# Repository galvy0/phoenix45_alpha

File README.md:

# Phoenix45 Alpha Stagger PCB
Alpha stagger version of Phoenix45.  

## PCB
### Layout Options

## Middle Column Options
The middle column can be configured with either an OLED or a trackpoint module.  

### Middle Column Cover
Either case, I provide the files for a cover along with plate option to mount the cover.  
Using the cover would help fill/cover up the space between the plate and the top of the case and make the middle column look more flush with the top of the case (a.k.a it's just for aesthetics).  
To use the cover, you need M2 screws and standoffs - I find ~6 mm is a good length for the standoffs, though 7 mm also works well and gives enough space for the trackpoint module.  

### Trackpoint module
The only TP module compatible with this is the two-piece module found in ThinkPad T440/T450/T460/T470/T480, P52s, X240, X250, X260 X270 (according to https://deskthority.net/wiki/TrackPoint_Hardware).  
I just bought some replacement T440/T450 keyboards from Ebay and scavanged the TP modules.  
Steps (Very rough - I will try to take some photos for better instructions next time I build this):  
1. Unscrew the casing for the TP module.
2. Install a TP cover. This can be done later.    
Depending on the thickness of the cover, you may want to have hex nuts between the module and the cover so the TP sticks out as little as possible (mainly for aesthetics).  
3. Desolder all the lines and reconnect them using flexible wires so you can readjust the position of the TP module with the TP PCB.  
4. Refer to the pinouts from Deskthority to connect the pins on the TP PCB to the keyboard PCB.  
 
5. With the plate standoffs pre-installed, position the TP PCB slanted through the middle column.  

6. Install the TP cover to the plate.  
After all is done, it would look something like this: 

## QMK Firmware
https://github.com/galvy0/qmk_firmware/tree/galvy/keyboards/galvy/jd45_alpha

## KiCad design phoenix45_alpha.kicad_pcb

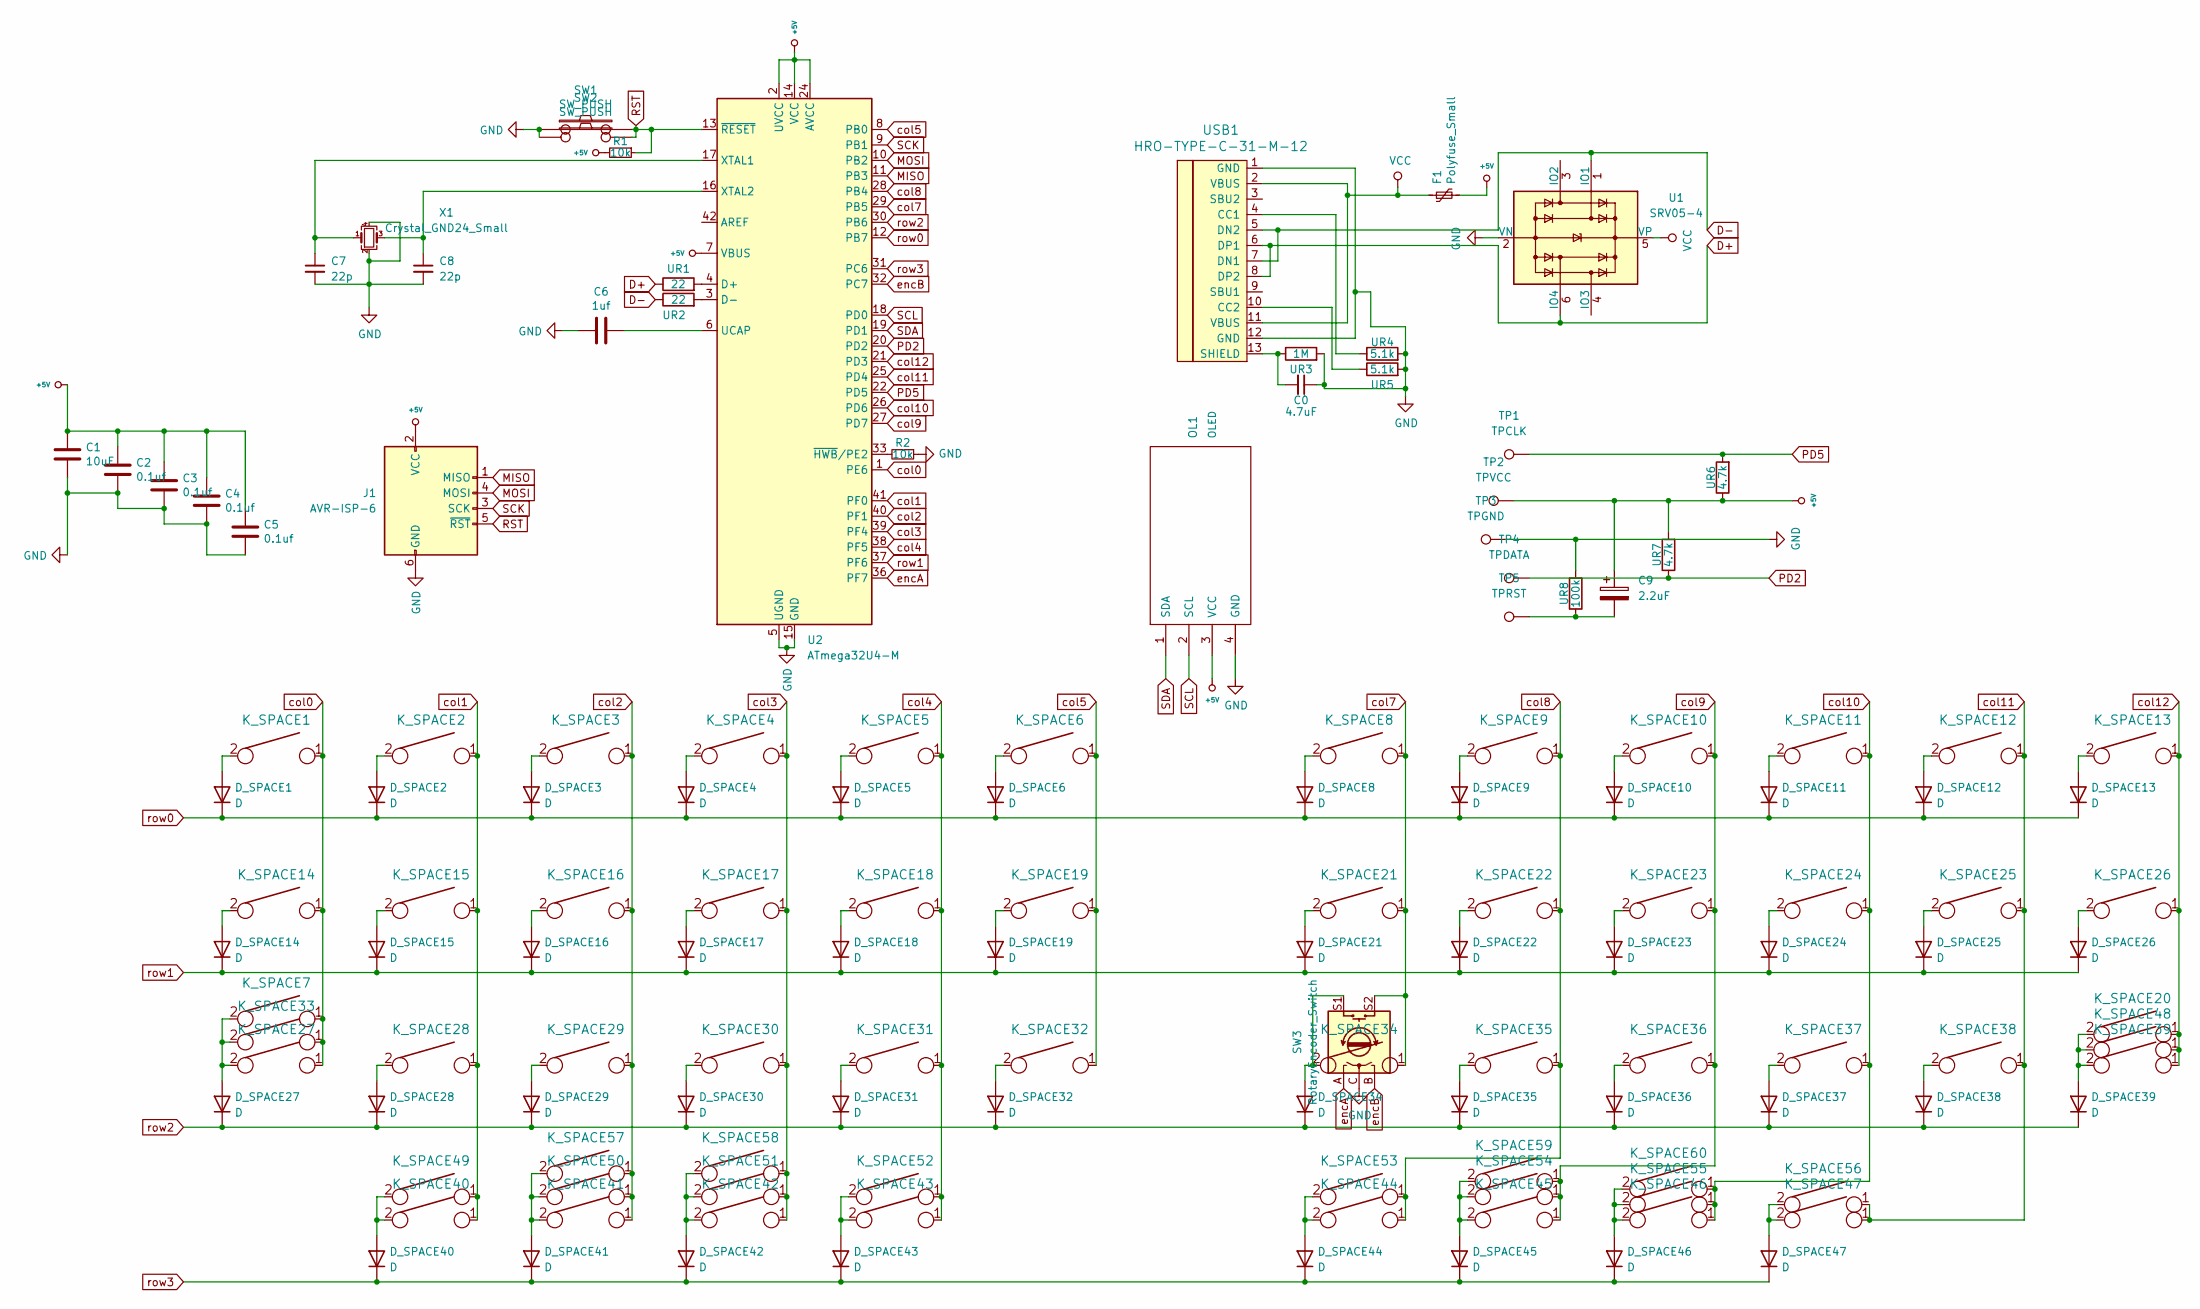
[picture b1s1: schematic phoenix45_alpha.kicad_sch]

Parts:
C0: 4.7uF; C_0805_2012Metric_Pad1.18x1.45mm_HandSolder
C1: 10uF; C_0805_2012Metric_Pad1.18x1.45mm_HandSolder
C2, C3, C4, C5: 0.1uf; C_0805_2012Metric_Pad1.18x1.45mm_HandSolder
C6: 1uf; C_0805_2012Metric_Pad1.18x1.45mm_HandSolder
C7, C8: 22p; C_0805_2012Metric_Pad1.18x1.45mm_HandSolder
C9: 2.2uF; C_0805_2012Metric_Pad1.18x1.45mm_HandSolder
D_SPACE1, D_SPACE2, D_SPACE3, D_SPACE4, D_SPACE5, D_SPACE6, D_SPACE8, D_SPACE9, D_SPACE10, D_SPACE11, D_SPACE12, D_SPACE13, D_SPACE14, D_SPACE15, D_SPACE16, D_SPACE17, D_SPACE18, D_SPACE19, D_SPACE21, D_SPACE22, D_SPACE23, D_SPACE24, D_SPACE25, D_SPACE26, D_SPACE27, D_SPACE28, D_SPACE29, D_SPACE30, D_SPACE31, D_SPACE32, D_SPACE34, D_SPACE35, D_SPACE36, D_SPACE37, D_SPACE38, D_SPACE39, D_SPACE40, D_SPACE41, D_SPACE42, D_SPACE43, D_SPACE44, D_SPACE45, D_SPACE46, D_SPACE47: D; D_SOD-123
F1: Polyfuse_Small; Fuse_1206_3216Metric_Pad1.42x1.75mm_HandSolder
J1: AVR-ISP-6; IDC-Header_2x03_P2.54mm_Vertical
K_SPACE1, K_SPACE2, K_SPACE3, K_SPACE4, K_SPACE5, K_SPACE6, K_SPACE8, K_SPACE9, K_SPACE10, K_SPACE11, K_SPACE12, K_SPACE13, K_SPACE14, K_SPACE15, K_SPACE16, K_SPACE17, K_SPACE18, K_SPACE19, K_SPACE21, K_SPACE22, K_SPACE23, K_SPACE24, K_SPACE25, K_SPACE26, K_SPACE27, K_SPACE28, K_SPACE29, K_SPACE30, K_SPACE31, K_SPACE32, K_SPACE34, K_SPACE35, K_SPACE36, K_SPACE37, K_SPACE38, K_SPACE39, K_SPACE41, K_SPACE46, K_SPACE50, K_SPACE51, K_SPACE54, K_SPACE55, K_SPACE58, K_SPACE59: KEYSW; MXOnly-1U-NoLED
K_SPACE7, K_SPACE20, K_SPACE52, K_SPACE53: KEYSW; MXOnly-1.5U-NoLED
K_SPACE33, K_SPACE40, K_SPACE42, K_SPACE45, K_SPACE47, K_SPACE48, K_SPACE57, K_SPACE60: KEYSW; MXOnly-1.25U-NoLED
K_SPACE43, K_SPACE44, K_SPACE49, K_SPACE56: KEYSW; MXOnly-1.75U-NoLED
OL1: OLED; OLED_v2
R1, R2: 10k; R_0805_2012Metric_Pad1.20x1.40mm_HandSolder
SW1, SW2: SW_PUSH; SW_SPST_SKQG_WithoutStem
SW3: RotaryEncoder_Switch; RotaryEncoder_Alps_EC11E-Switch_Vertical_H20mm
TP1: TPCLK; TestPoint_THTPad_1.0x1.0mm_Drill0.5mm
TP2: TPVCC; TestPoint_THTPad_1.0x1.0mm_Drill0.5mm
TP3: TPGND; TestPoint_THTPad_1.0x1.0mm_Drill0.5mm
TP4: TPDATA; TestPoint_THTPad_1.0x1.0mm_Drill0.5mm
TP5: TPRST; TestPoint_THTPad_1.0x1.0mm_Drill0.5mm
U1: SRV05-4; SOT-23-6_Handsoldering
U2: ATmega32U4-M; QFN-44-1EP_7x7mm_P0.5mm_EP5.2x5.2mm_ThermalVias
UR1, UR2: 22; R_0805_2012Metric_Pad1.20x1.40mm_HandSolder
UR3: 1M; R_0805_2012Metric_Pad1.20x1.40mm_HandSolder
UR4, UR5: 5.1k; R_0805_2012Metric_Pad1.20x1.40mm_HandSolder
UR6, UR7: 4.7k; R_0805_2012Metric_Pad1.20x1.40mm_HandSolder
UR8: 100k; R_0805_2012Metric_Pad1.20x1.40mm_HandSolder
USB1: HRO-TYPE-C-31-M-12; HRO-TYPE-C-31-M-12-HandSoldering
X1: Crystal_GND24_Small; Crystal_SMD_3225-4Pin_3.2x2.5mm_HandSoldering

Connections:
+5V: C1.1, C2.1, C3.1, C4.1, C5.1, C9.1, F1.2, J1.2 (VCC), OL1.3 (VCC), R1.2, TP2.1, U2.2 (UVCC), U2.7 (VBUS), U2.14 (VCC), U2.24 (AVCC), U2.34 (VCC), U2.44 (AVCC), UR6.1, UR7.2
D+: U1.6 (IO4), UR2.1, USB1.6 (DP1), USB1.8 (DP2)
D-: U1.1 (IO1), UR1.1, USB1.5 (DN2), USB1.7 (DN1)
GND: C0.1, C1.2, C2.2, C3.2, C4.2, C5.2, C6.2, C7.2, C8.2, J1.6 (GND), OL1.4 (GND), R2.1, SW1.1, SW2.1, SW3.C, TP3.1, U1.2 (VN), U2.5 (UGND), U2.15 (GND), U2.23 (GND), U2.35 (GND), U2.43 (GND), U2.45 (GND), UR3.2, UR4.2, UR5.2, UR8.2, USB1.1 (GND), USB1.12 (GND), X1.2, X1.4
MISO: J1.1 (MISO), U2.11 (PB3)
MOSI: J1.4 (MOSI), U2.10 (PB2)
unnamed: C0.2, UR3.1, USB1.13 (SHIELD)
unnamed: C6.1, U2.6 (UCAP)
unnamed: C7.1, U2.17 (XTAL1), X1.1
unnamed: C8.1, U2.16 (XTAL2), X1.3
unnamed: C9.2, TP5.1, UR8.1
unnamed: D_SPACE1.2 (A), K_SPACE1.2
unnamed: D_SPACE2.2 (A), K_SPACE2.2
unnamed: D_SPACE3.2 (A), K_SPACE3.2
unnamed: D_SPACE4.2 (A), K_SPACE4.2
unnamed: D_SPACE5.2 (A), K_SPACE5.2
unnamed: D_SPACE6.2 (A), K_SPACE6.2
unnamed: D_SPACE8.2 (A), K_SPACE8.2
unnamed: D_SPACE9.2 (A), K_SPACE9.2
unnamed: D_SPACE10.2 (A), K_SPACE10.2
unnamed: D_SPACE11.2 (A), K_SPACE11.2
unnamed: D_SPACE12.2 (A), K_SPACE12.2
unnamed: D_SPACE13.2 (A), K_SPACE13.2
unnamed: D_SPACE14.2 (A), K_SPACE14.2
unnamed: D_SPACE15.2 (A), K_SPACE15.2
unnamed: D_SPACE16.2 (A), K_SPACE16.2
unnamed: D_SPACE17.2 (A), K_SPACE17.2
unnamed: D_SPACE18.2 (A), K_SPACE18.2
unnamed: D_SPACE19.2 (A), K_SPACE19.2
unnamed: D_SPACE21.2 (A), K_SPACE21.2
unnamed: D_SPACE22.2 (A), K_SPACE22.2
unnamed: D_SPACE23.2 (A), K_SPACE23.2
unnamed: D_SPACE24.2 (A), K_SPACE24.2
unnamed: D_SPACE25.2 (A), K_SPACE25.2
unnamed: D_SPACE26.2 (A), K_SPACE26.2
unnamed: D_SPACE27.2 (A), K_SPACE7.2, K_SPACE27.2, K_SPACE33.2
unnamed: D_SPACE28.2 (A), K_SPACE28.2
unnamed: D_SPACE29.2 (A), K_SPACE29.2
unnamed: D_SPACE30.2 (A), K_SPACE30.2
unnamed: D_SPACE31.2 (A), K_SPACE31.2
unnamed: D_SPACE32.2 (A), K_SPACE32.2
unnamed: D_SPACE34.2 (A), K_SPACE34.2, SW3.S1
unnamed: D_SPACE35.2 (A), K_SPACE35.2
unnamed: D_SPACE36.2 (A), K_SPACE36.2
unnamed: D_SPACE37.2 (A), K_SPACE37.2
unnamed: D_SPACE38.2 (A), K_SPACE38.2
unnamed: D_SPACE39.2 (A), K_SPACE20.2, K_SPACE39.2, K_SPACE48.2
unnamed: D_SPACE40.2 (A), K_SPACE40.2, K_SPACE49.2
unnamed: D_SPACE41.2 (A), K_SPACE41.2, K_SPACE50.2, K_SPACE57.2
unnamed: D_SPACE42.2 (A), K_SPACE42.2, K_SPACE51.2, K_SPACE58.2
unnamed: D_SPACE43.2 (A), K_SPACE43.2, K_SPACE52.2
unnamed: D_SPACE44.2 (A), K_SPACE44.2, K_SPACE53.2
unnamed: D_SPACE45.2 (A), K_SPACE45.2, K_SPACE54.2, K_SPACE59.2
unnamed: D_SPACE46.2 (A), K_SPACE46.2, K_SPACE55.2, K_SPACE60.2
unnamed: D_SPACE47.2 (A), K_SPACE47.2, K_SPACE56.2
unnamed: R2.2, U2.33 (~HWB/PE2)
unnamed: U2.3 (D-), UR1.2
unnamed: U2.4 (D+), UR2.2
unnamed: UR4.1, USB1.4 (CC1)
unnamed: UR5.1, USB1.10 (CC2)
PD2: TP4.1, U2.20 (PD2), UR7.1
PD5: TP1.1, U2.22 (PD5), UR6.2
RST: J1.5 (~RST), R1.1, SW1.2, SW2.2, U2.13 (~RESET)
SCK: J1.3 (SCK), U2.9 (PB1)
SCL: OL1.2 (SCL), U2.18 (PD0)
SDA: OL1.1 (SDA), U2.19 (PD1)
VCC: F1.1, U1.5 (VP), USB1.2 (VBUS), USB1.11 (VBUS)
col0: K_SPACE1.1, K_SPACE7.1, K_SPACE14.1, K_SPACE27.1, K_SPACE33.1, U2.1 (PE6)
col1: K_SPACE2.1, K_SPACE15.1, K_SPACE28.1, K_SPACE40.1, K_SPACE49.1, U2.41 (PF0)
col2: K_SPACE3.1, K_SPACE16.1, K_SPACE29.1, K_SPACE41.1, K_SPACE50.1, K_SPACE57.1, U2.40 (PF1)
col3: K_SPACE4.1, K_SPACE17.1, K_SPACE30.1, K_SPACE42.1, K_SPACE51.1, K_SPACE58.1, U2.39 (PF4)
col4: K_SPACE5.1, K_SPACE18.1, K_SPACE31.1, K_SPACE43.1, K_SPACE52.1, U2.38 (PF5)
col5: K_SPACE6.1, K_SPACE19.1, K_SPACE32.1, U2.8 (PB0)
col7: K_SPACE8.1, K_SPACE21.1, K_SPACE34.1, SW3.S2, U2.29 (PB5)
col8: K_SPACE9.1, K_SPACE22.1, K_SPACE35.1, K_SPACE44.1, K_SPACE53.1, U2.28 (PB4)
col9: K_SPACE10.1, K_SPACE23.1, K_SPACE36.1, K_SPACE45.1, K_SPACE54.1, K_SPACE59.1, U2.27 (PD7)
col10: K_SPACE11.1, K_SPACE24.1, K_SPACE37.1, K_SPACE46.1, K_SPACE55.1, K_SPACE60.1, U2.26 (PD6)
col11: K_SPACE12.1, K_SPACE25.1, K_SPACE38.1, K_SPACE47.1, K_SPACE56.1, U2.25 (PD4)
col12: K_SPACE13.1, K_SPACE20.1, K_SPACE26.1, K_SPACE39.1, K_SPACE48.1, U2.21 (PD3)
encA: SW3.A, U2.36 (PF7)
encB: SW3.B, U2.32 (PC7)
row0: D_SPACE1.1 (K), D_SPACE2.1 (K), D_SPACE3.1 (K), D_SPACE4.1 (K), D_SPACE5.1 (K), D_SPACE6.1 (K), D_SPACE8.1 (K), D_SPACE9.1 (K), D_SPACE10.1 (K), D_SPACE11.1 (K), D_SPACE12.1 (K), D_SPACE13.1 (K), U2.12 (PB7)
row1: D_SPACE14.1 (K), D_SPACE15.1 (K), D_SPACE16.1 (K), D_SPACE17.1 (K), D_SPACE18.1 (K), D_SPACE19.1 (K), D_SPACE21.1 (K), D_SPACE22.1 (K), D_SPACE23.1 (K), D_SPACE24.1 (K), D_SPACE25.1 (K), D_SPACE26.1 (K), U2.37 (PF6)
row2: D_SPACE27.1 (K), D_SPACE28.1 (K), D_SPACE29.1 (K), D_SPACE30.1 (K), D_SPACE31.1 (K), D_SPACE32.1 (K), D_SPACE34.1 (K), D_SPACE35.1 (K), D_SPACE36.1 (K), D_SPACE37.1 (K), D_SPACE38.1 (K), D_SPACE39.1 (K), U2.30 (PB6)
row3: D_SPACE40.1 (K), D_SPACE41.1 (K), D_SPACE42.1 (K), D_SPACE43.1 (K), D_SPACE44.1 (K), D_SPACE45.1 (K), D_SPACE46.1 (K), D_SPACE47.1 (K), U2.31 (PC6)

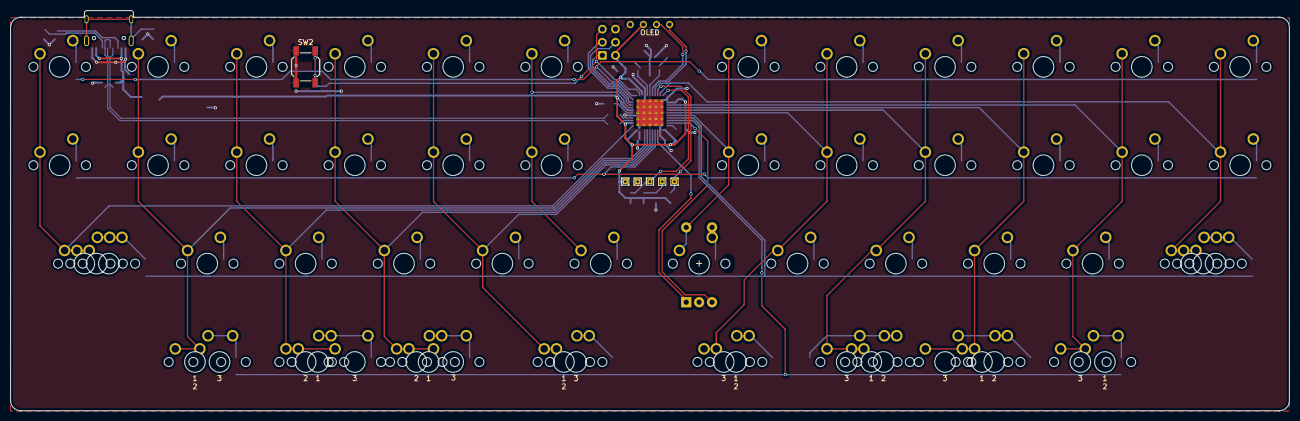
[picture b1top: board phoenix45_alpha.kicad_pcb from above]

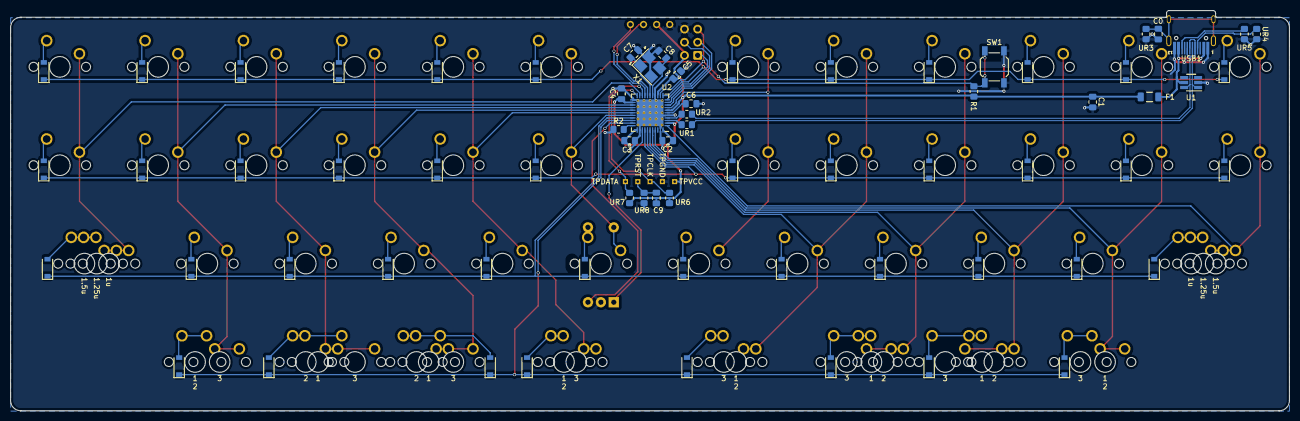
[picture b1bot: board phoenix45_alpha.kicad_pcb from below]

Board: 2 copper layers, 247.7 x 77.5 mm, 139 parts (71 on the bottom side), 85 nets.

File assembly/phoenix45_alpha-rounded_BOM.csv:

sep=;
"Id";"Designator";"Package";"Quantity";"Designation";"Supplier and ref";
1;"K_SPACE30,K_SPACE31,K_SPACE38,K_SPACE22,K_SPACE11,K_SPACE39,K_SPACE1,K_SPACE46,K_SPACE50,K_SPACE12,K_SPACE10,K_SPACE37,K_SPACE24,K_SPACE9,K_SPACE15,K_SPACE55,K_SPACE51,K_SPACE17,K_SPACE34,K_SPACE41,K_SPACE16,K_SPACE25,K_SPACE59,K_SPACE21,K_SPACE28,K_SPACE35,K_SPACE6,K_SPACE14,K_SPACE54,K_SPACE3,K_SPACE58,K_SPACE19,K_SPACE13,K_SPACE5,K_SPACE26,K_SPACE36,K_SPACE18,K_SPACE8,K_SPACE27,K_SPACE32,K_SPACE29,K_SPACE23,K_SPACE2,K_SPACE4";"MXOnly-1U-NoLED";44;"KEYSW";;;
2;"K_SPACE40,K_SPACE42,K_SPACE57,K_SPACE33,K_SPACE48,K_SPACE47,K_SPACE45,K_SPACE60";"MXOnly-1.25U-NoLED";8;"KEYSW";;;
3;"K_SPACE56,K_SPACE49,K_SPACE43,K_SPACE44";"MXOnly-1.75U-NoLED";4;"KEYSW";;;
4;"SW3";"RotaryEncoder_Alps_EC11E-Switch_Vertical_H20mm";1;"RotaryEncoder_Switch";;;
5;"SW2,SW1";"SW_SPST_SKQG_WithoutStem";2;"SW_PUSH";;;
6;"TP1";"TestPoint_THTPad_1.0x1.0mm_Drill0.5mm";1;"TPCLK";;;
7;"TP3";"TestPoint_THTPad_1.0x1.0mm_Drill0.5mm";1;"TPGND";;;
8;"TP2";"TestPoint_THTPad_1.0x1.0mm_Drill0.5mm";1;"TPVCC";;;
9;"TP5";"TestPoint_THTPad_1.0x1.0mm_Drill0.5mm";1;"TPRST";;;
10;"K_SPACE52,K_SPACE7,K_SPACE20,K_SPACE53";"MXOnly-1.5U-NoLED";4;"KEYSW";;;
11;"TP4";"TestPoint_THTPad_1.0x1.0mm_Drill0.5mm";1;"TPDATA";;;
12;"OL1";"OLED_v2";1;"OLED";;;
13;"D_SPACE29,D_SPACE30,D_SPACE44,D_SPACE26,D_SPACE22,D_SPACE16,D_SPACE13,D_SPACE43,D_SPACE45,D_SPACE25,D_SPACE28,D_SPACE39,D_SPACE2,D_SPACE14,D_SPACE46,D_SPACE11,D_SPACE4,D_SPACE8,D_SPACE19,D_SPACE42,D_SPACE12,D_SPACE23,D_SPACE34,D_SPACE36,D_SPACE32,D_SPACE3,D_SPACE24,D_SPACE31,D_SPACE37,D_SPACE38,D_SPACE10,D_SPACE6,D_SPACE5,D_SPACE27,D_SPACE41,D_SPACE35,D_SPACE21,D_SPACE18,D_SPACE9,D_SPACE17,D_SPACE15,D_SPACE1,D_SPACE40,D_SPACE47";"D_SOD-123";44;"D";;;
14;"UR2,UR1";"R_0805_2012Metric_Pad1.20x1.40mm_HandSolder";2;"22";;;
15;"X1";"Crystal_SMD_3225-4Pin_3.2x2.5mm_HandSoldering";1;"Crystal_GND24_Small";;;
16;"C0";"C_0805_2012Metric_Pad1.18x1.45mm_HandSolder";1;"4.7uF";;;
17;"C2,C4,C5,C3";"C_0805_2012Metric_Pad1.18x1.45mm_HandSolder";4;"0.1uf";;;
18;"R2,R1";"R_0805_2012Metric_Pad1.20x1.40mm_HandSolder";2;"10k";;;
19;"U2";"QFN-44-1EP_7x7mm_P0.5mm_EP5.2x5.2mm_ThermalVias";1;"ATmega32U4-M";;;
20;"C8,C7";"C_0805_2012Metric_Pad1.18x1.45mm_HandSolder";2;"22p";;;
21;"C6";"C_0805_2012Metric_Pad1.18x1.45mm_HandSolder";1;"1uf";;;
22;"UR3";"R_0805_2012Metric_Pad1.20x1.40mm_HandSolder";1;"1M";;;
23;"C1";"C_0805_2012Metric_Pad1.18x1.45mm_HandSolder";1;"10uF";;;
24;"UR4,UR5";"R_0805_2012Metric_Pad1.20x1.40mm_HandSolder";2;"5.1k";;;
25;"C9";"C_0805_2012Metric_Pad1.18x1.45mm_HandSolder";1;"2.2uF";;;
26;"UR8";"R_0805_2012Metric_Pad1.20x1.40mm_HandSolder";1;"100k";;;
27;"USB1";"HRO-TYPE-C-31-M-12-HandSoldering";1;"HRO-TYPE-C-31-M-12";;;
28;"J1";"IDC-Header_2x03_P2.54mm_Vertical";1;"AVR-ISP-6";;;
29;"U1";"SOT-23-6_Handsoldering";1;"SRV05-4";;;
30;"U3";"TQFP-44_10x10mm_P0.8mm";1;"ATmega32U4-M";;;
31;"UR7,UR6";"R_0805_2012Metric_Pad1.20x1.40mm_HandSolder";2;"4.7k";;;
32;"F1";"Fuse_1206_3216Metric_Pad1.42x1.75mm_HandSolder";1;"Polyfuse_Small";;;

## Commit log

2022-07-31 init
2022-07-31 change name to alpha
2022-08-01 added avr
2022-08-01 v1 finished
2022-08-07 trackpoint
2022-08-07 qfn + tqfp
2022-08-08 Move TP connectors to front
2022-08-10 round tracks
2022-08-12 assembly
2022-08-12 MX+choc
2022-08-31 plates
2022-09-10 go back to MX
2022-09-11 improve trackpoint compatibility; multiple bottom rows, final touch up
2022-09-12 assembly prep
2022-09-12 atmega32u4-MU only
2022-09-12 cleanup
2022-09-13 minor adjustments
2022-09-13 final touch up
2023-03-12 files
